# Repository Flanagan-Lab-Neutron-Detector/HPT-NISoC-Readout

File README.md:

# HPT-NISoC-Readout
PCB files for HighPoint Design's NISoC readout board (P/N 31813).

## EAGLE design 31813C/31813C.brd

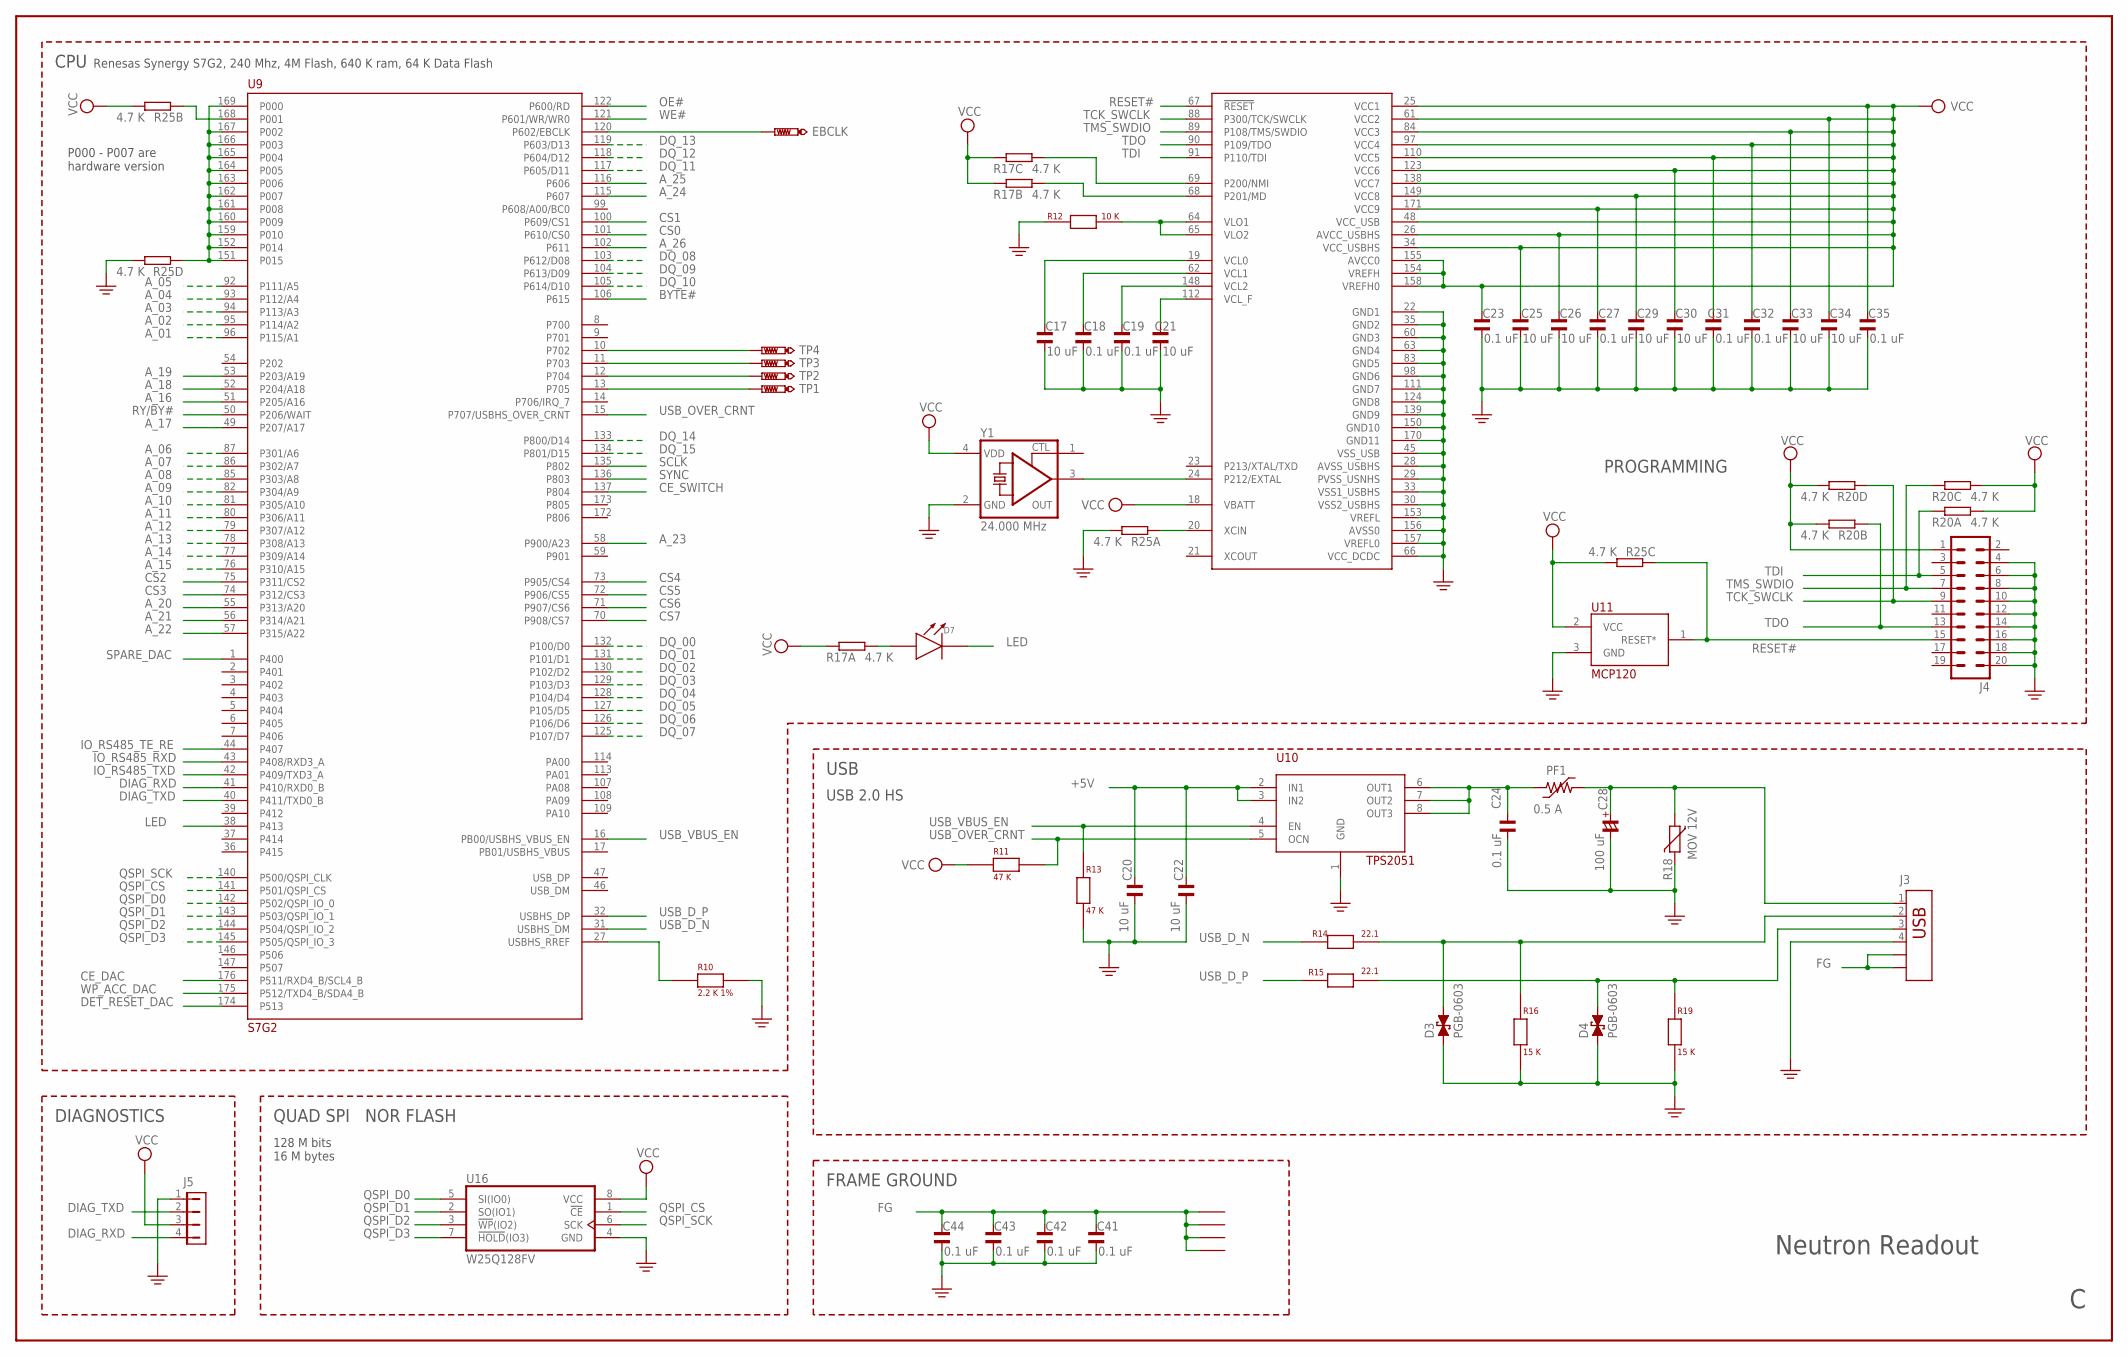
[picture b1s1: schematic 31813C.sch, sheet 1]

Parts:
C17, C20, C21, C22, C25, C26, C29, C30, C33, C34: 10 uF; 0603
C18, C19, C23, C24, C27, C31, C32, C35, C41, C42, C43, C44: 0.1 uF; 0603
C28: 100 uF; CSV-E/F
D3, D4: PGB-0603
D7: LED0805; D0805
EBCLK: TP; TP8040
J3: CON-USB-292303-1; USB
J4: ML20
J5: MTA04; MTA04-100
M1, M2, M3, M4: MNT-125
PF1: 0.5 A; F1206
R10: 2.2 K 1%; 0603
R11, R13: 47 K; 0603
R12: 10 K; 0603
R14, R15: 22.1; 0603
R16, R19: 15 K; 0603
R17, R20, R25: 4.7 K; RNET-4R-38V
R18: MOV 12V; R0603
TP1, TP2, TP3, TP4: TP; TP8040
U9: S7G2; LQFP176
U10: TPS2051; SOIC-8-SPECIAL
U11: MCP120; SOT23
U16: W25Q128FV; SO08-JB
Y1: 24.000 MHz; ASFL1

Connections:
+5V: C20.2, C22.2, U10.2 (IN1), U10.3 (IN2); also elsewhere on the board
A_01: U9.96 (P115/A1); also elsewhere on the board
A_02: U9.95 (P114/A2); also elsewhere on the board
A_03: U9.94 (P113/A3); also elsewhere on the board
A_04: U9.93 (P112/A4); also elsewhere on the board
A_05: U9.92 (P111/A5); also elsewhere on the board
A_06: U9.87 (P301/A6); also elsewhere on the board
A_07: U9.86 (P302/A7); also elsewhere on the board
A_08: U9.85 (P303/A8); also elsewhere on the board
A_09: U9.82 (P304/A9); also elsewhere on the board
A_10: U9.81 (P305/A10); also elsewhere on the board
A_11: U9.80 (P306/A11); also elsewhere on the board
A_12: U9.79 (P307/A12); also elsewhere on the board
A_13: U9.78 (P308/A13); also elsewhere on the board
A_14: U9.77 (P309/A14); also elsewhere on the board
A_15: U9.76 (P310/A15); also elsewhere on the board
A_16: U9.51 (P205/A16); also elsewhere on the board
A_17: U9.49 (P207/A17); also elsewhere on the board
A_18: U9.52 (P204/A18); also elsewhere on the board
A_19: U9.53 (P203/A19); also elsewhere on the board
A_20: U9.55 (P313/A20); also elsewhere on the board
A_21: U9.56 (P314/A21); also elsewhere on the board
A_22: U9.57 (P315/A22); also elsewhere on the board
A_23: U9.58 (P900/A23); also elsewhere on the board
A_24: U9.115 (P607); also elsewhere on the board
A_25: U9.116 (P606); also elsewhere on the board
A_26: U9.102 (P611); also elsewhere on the board
BYTE#: U9.106 (P615); also elsewhere on the board
CE_DAC: U9.176 (P511/RXD4_B/SCL4_B); also elsewhere on the board
CE_SWITCH: U9.137 (P804); also elsewhere on the board
CS0: U9.101 (P610/CS0); also elsewhere on the board
CS1: U9.100 (P609/CS1); also elsewhere on the board
CS2: U9.75 (P311/CS2); also elsewhere on the board
CS3: U9.74 (P312/CS3); also elsewhere on the board
CS4: U9.73 (P905/CS4); also elsewhere on the board
CS5: U9.72 (P906/CS5); also elsewhere on the board
CS6: U9.71 (P907/CS6); also elsewhere on the board
CS7: U9.70 (P908/CS7); also elsewhere on the board
DET_RESET_DAC: U9.174 (P513); also elsewhere on the board
DIAG_RXD: J5.4, U9.41 (P410/RXD0_B)
DIAG_TXD: J5.2, U9.40 (P411/TXD0_B)
DQ_00: U9.132 (P100/D0); also elsewhere on the board
DQ_01: U9.131 (P101/D1); also elsewhere on the board
DQ_02: U9.130 (P102/D2); also elsewhere on the board
DQ_03: U9.129 (P103/D3); also elsewhere on the board
DQ_04: U9.128 (P104/D4); also elsewhere on the board
DQ_05: U9.127 (P105/D5); also elsewhere on the board
DQ_06: U9.126 (P106/D6); also elsewhere on the board
DQ_07: U9.125 (P107/D7); also elsewhere on the board
DQ_08: U9.103 (P612/D08); also elsewhere on the board
DQ_09: U9.104 (P613/D09); also elsewhere on the board
DQ_10: U9.105 (P614/D10); also elsewhere on the board
DQ_11: U9.117 (P605/D11); also elsewhere on the board
DQ_12: U9.118 (P604/D12); also elsewhere on the board
DQ_13: U9.119 (P603/D13); also elsewhere on the board
DQ_14: U9.133 (P800/D14); also elsewhere on the board
DQ_15: U9.134 (P801/D15); also elsewhere on the board
FG: C41.2, C42.2, C43.2, C44.2, J3.S1, J3.S2, M1.1, M2.1, M3.1, M4.1
GND: C17.1, C18.1, C19.1, C20.1, C21.1, C22.1, C23.1, C24.1, C25.1, C26.1, C27.1, C28.-, C29.1, C30.1, C31.1, C32.1, C33.1, C34.1, C35.1, C41.1, C42.1, C43.1, C44.1, D3.1, D4.1, J3.4, J4.4, J4.6, J4.8, J4.10, J4.12, J4.14, J4.16, J4.18, J4.20, J5.1, R10.2, R12.1, R13.1, R16.1, R18.2, R19.1, R25.5 (2), R25.8 (2), U9.22 (GND1), U9.28 (AVSS_USBHS), U9.29 (PVSS_USNHS), U9.30 (VSS2_USBHS), U9.33 (VSS1_USBHS), U9.35 (GND2), U9.45 (VSS_USB), U9.60 (GND3), U9.63 (GND4), U9.66 (VCC_DCDC), U9.83 (GND5), U9.98 (GND6), U9.111 (GND7), U9.124 (GND8), U9.139 (GND9), U9.150 (GND10), U9.153 (VREFL), U9.156 (AVSS0), U9.157 (VREFL0), U9.170 (GND11), U10.1 (GND), U11.3 (GND), U16.4 (GND), Y1.2 (GND); also elsewhere on the board
IO_RS485_RXD: U9.43 (P408/RXD3_A); also elsewhere on the board
IO_RS485_TE_RE: U9.44 (P407); also elsewhere on the board
IO_RS485_TXD: U9.42 (P409/TXD3_A); also elsewhere on the board
LED: D7.C (1), U9.38 (P413)
unnamed: R12.2, U9.64 (VLO1), U9.65 (VLO2)
unnamed: R17.7 (2), U9.68 (P201/MD)
unnamed: R17.6 (2), U9.69 (P200/NMI)
unnamed: C17.2, U9.19 (VCL0)
unnamed: C18.2, U9.62 (VCL1)
unnamed: C19.2, U9.148 (VCL2)
unnamed: C21.2, U9.112 (VCL_F)
unnamed: U9.24 (P212/EXTAL), Y1.3 (OUT)
unnamed: C24.2, PF1.1, U10.6 (OUT1), U10.7 (OUT2), U10.8 (OUT3)
unnamed: C28.+, J3.1, PF1.2, R18.1
unnamed: D3.2, J3.2, R14.2, R16.2
unnamed: R10.1, U9.27 (USBHS_RREF)
unnamed: D4.2, J3.3, R15.2, R19.2
unnamed: TP3.1, U9.11 (P703)
unnamed: TP4.1, U9.10 (P702)
unnamed: TP1.1, U9.13 (P705)
unnamed: TP2.1, U9.12 (P704)
unnamed: R25.1, U9.20 (XCIN)
unnamed: D7.A (2), R17.8 (2)
unnamed: R25.2 (1), U9.168 (P001)
unnamed: R25.4 (1), U9.151 (P015), U9.152 (P014), U9.159 (P010), U9.160 (P009), U9.161 (P008), U9.162 (P007), U9.163 (P006), U9.164 (P005), U9.165 (P004), U9.166 (P003), U9.167 (P002), U9.169 (P000)
unnamed: EBCLK.1, U9.120 (P602/EBCLK)
OE#: U9.122 (P600/RD); also elsewhere on the board
QSPI_CS: U9.141 (P501/QSPI_CS), U16.1 (!CE!)
QSPI_D0: U9.142 (P502/QSPI_IO_0), U16.5 (SI(IO0))
QSPI_D1: U9.143 (P503/QSPI_IO_1), U16.2 (SO(IO1))
QSPI_D2: U9.144 (P504/QSPI_IO_2), U16.3 (!WP!(IO2))
QSPI_D3: U9.145 (P505/QSPI_IO_3), U16.7 (!HOLD!(IO3))
QSPI_SCK: U9.140 (P500/QSPI_CLK), U16.6 (SCK)
RESET#: J4.15, R25.3 (1), U9.67 (!RESET), U11.1 (RESET*)
RY/BY#: U9.50 (P206/WAIT); also elsewhere on the board
SCLK: U9.135 (P802); also elsewhere on the board
SPARE_DAC: U9.1 (P400); also elsewhere on the board
SYNC: U9.136 (P803); also elsewhere on the board
TCK_SWCLK: J4.9, R20.4 (1), U9.88 (P300/TCK/SWCLK)
TDI: J4.5, R20.1, U9.91 (P110/TDI)
TDO: J4.13, R20.2 (1), U9.90 (P109/TDO)
TMS_SWDIO: J4.7, R20.3 (1), U9.89 (P108/TMS/SWDIO)
USB_D_N: R14.1, U9.31 (USBHS_DM)
USB_D_P: R15.1, U9.32 (USBHS_DP)
USB_OVER_CRNT: R11.2, U9.15 (P707/USBHS_OVER_CRNT), U10.5 (OCN)
USB_VBUS_EN: R13.2, U9.16 (PB00/USBHS_VBUS_EN), U10.4 (EN)
VCC: C23.2, C25.2, C26.2, C27.2, C29.2, C30.2, C31.2, C32.2, C33.2, C34.2, C35.2, J4.1, J5.3, R11.1, R17.1, R17.2 (1), R17.3 (1), R20.5 (2), R20.6 (2), R20.7 (2), R20.8 (2), R25.6 (2), R25.7 (2), U9.18 (VBATT), U9.25 (VCC1), U9.26 (AVCC_USBHS), U9.34 (VCC_USBHS), U9.48 (VCC_USB), U9.61 (VCC2), U9.84 (VCC3), U9.97 (VCC4), U9.110 (VCC5), U9.123 (VCC6), U9.138 (VCC7), U9.149 (VCC8), U9.154 (VREFH), U9.155 (AVCC0), U9.158 (VREFH0), U9.171 (VCC9), U11.2 (VCC), U16.8 (VCC), Y1.4 (VDD); also elsewhere on the board
WE#: U9.121 (P601/WR/WR0); also elsewhere on the board
WP_ACC_DAC: U9.175 (P512/TXD4_B/SDA4_B); also elsewhere on the board

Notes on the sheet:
PROGRAMMING
CPU
Renesas Synergy S7G2, 240 Mhz, 4M Flash, 640 K ram, 64 K Data Flash
Neutron Readout
USB
QUAD SPI NOR FLASH
128 M bits 16 M bytes
DIAGNOSTICS
FRAME GROUND
USB 2.0 HS
P000 - P007 are hardware version

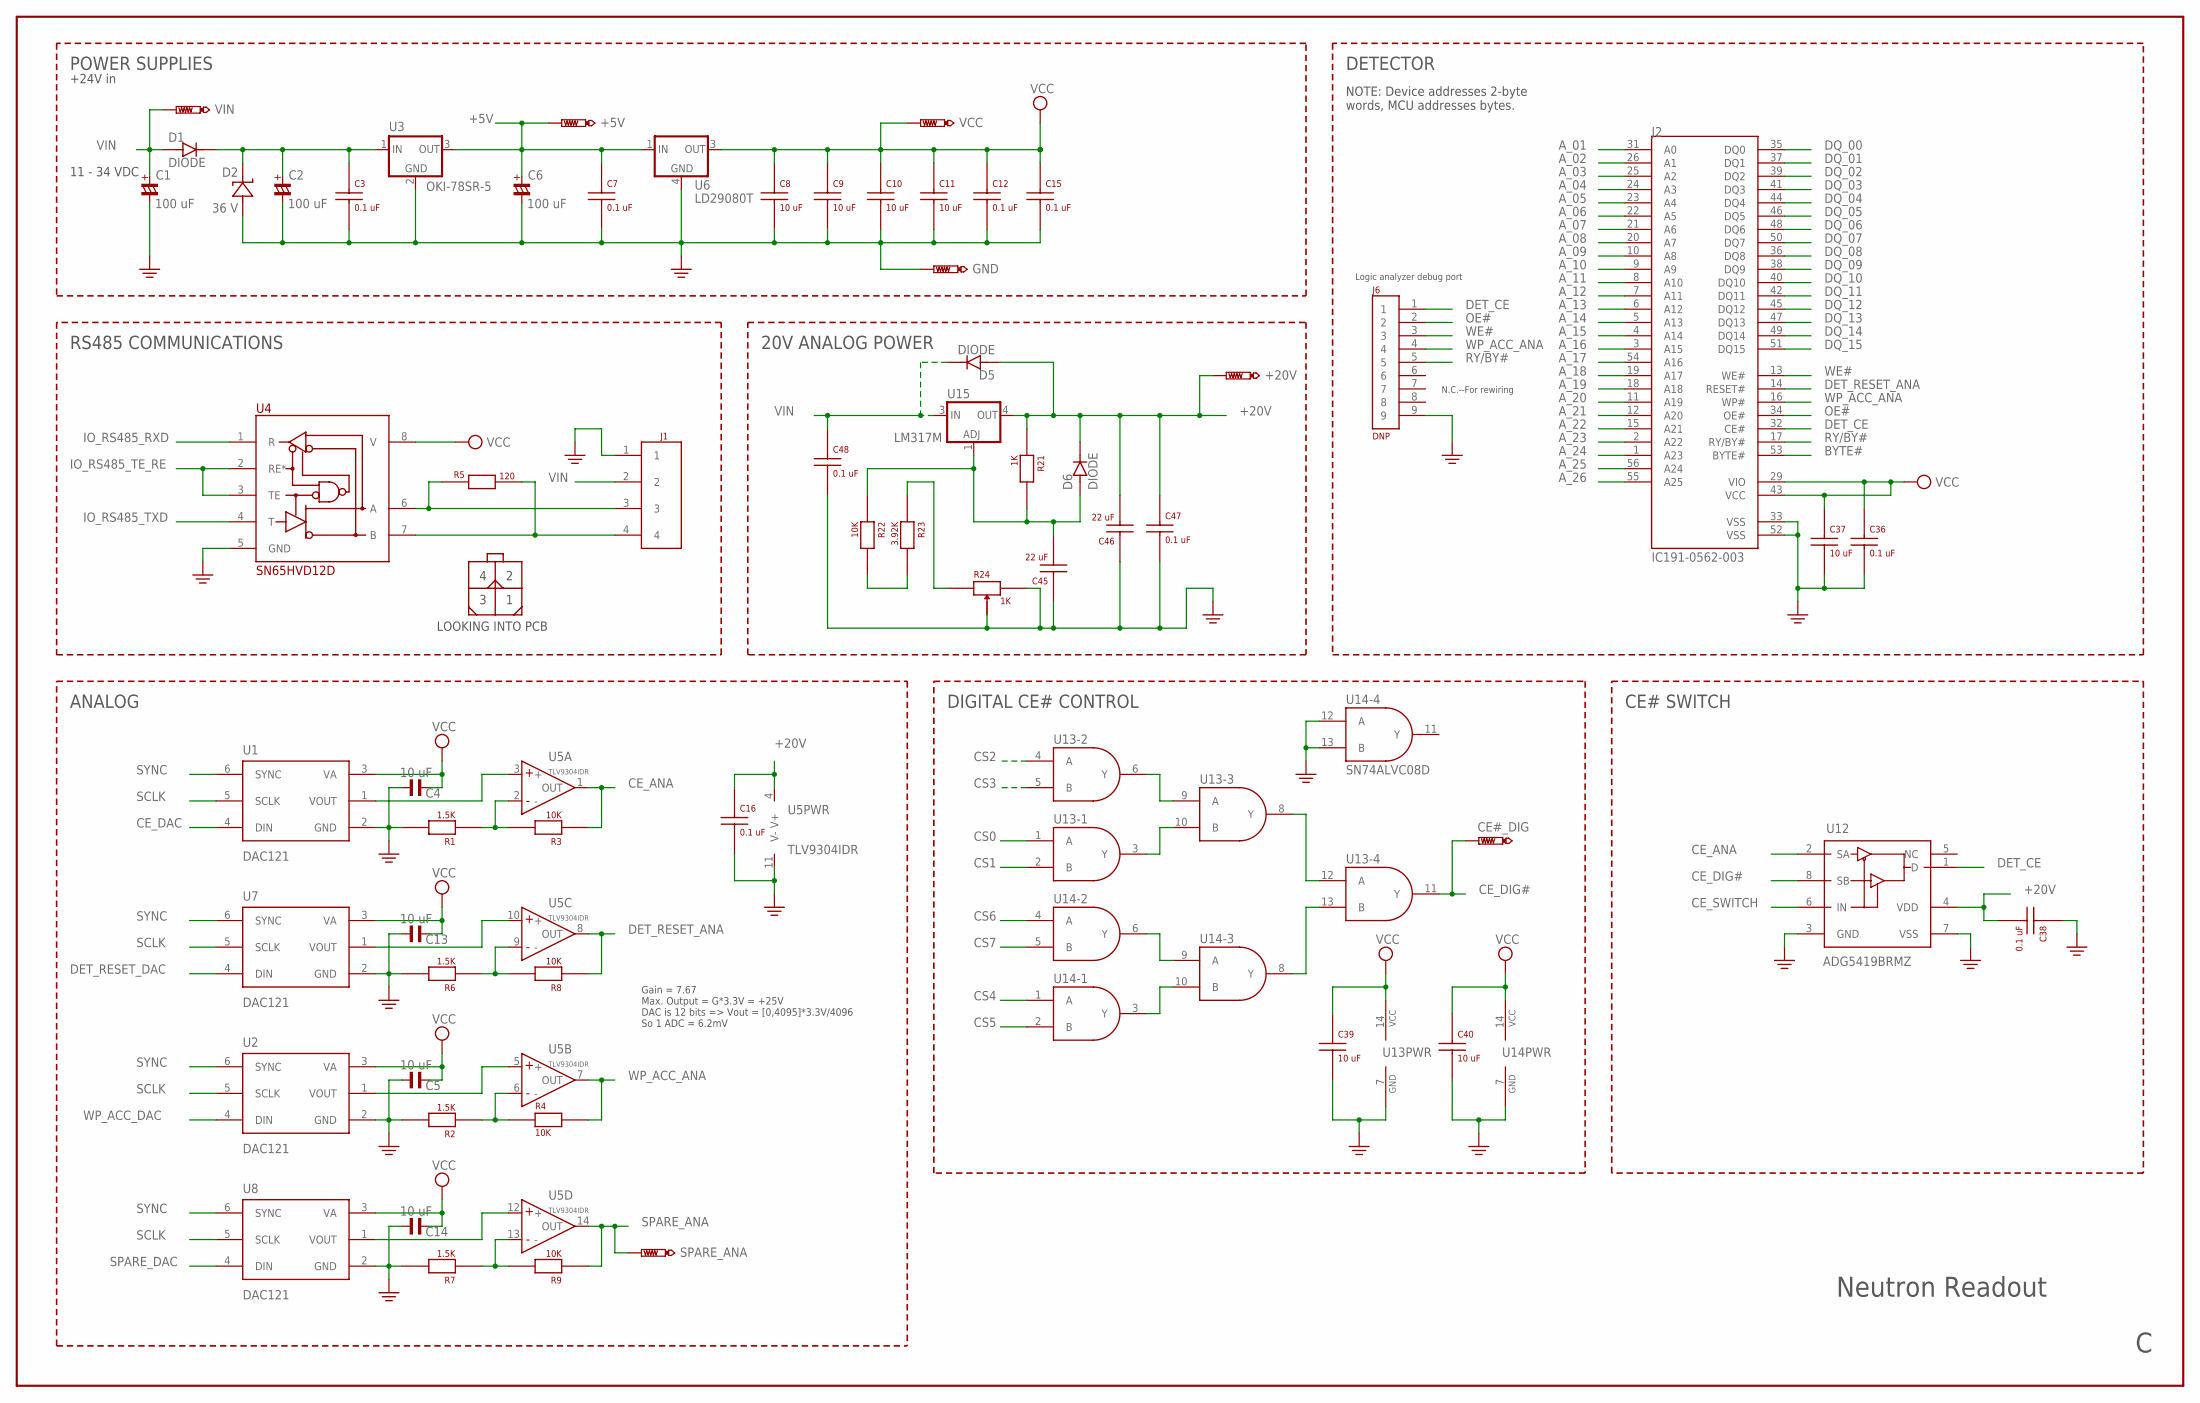
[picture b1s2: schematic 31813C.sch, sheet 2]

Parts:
+5V, +20V: TP; TP8040
C1, C2, C6: 100 uF; CSV-E/F
C3, C7, C12, C15, C16, C36, C38, C47, C48: 0.1 uF; 0603
C4, C5, C8, C9, C10, C11, C13, C14, C37, C39, C40: 10 uF; 0603
C45, C46: 22 uF; C1206
CE#_DIG: TP; TP8040
D1, D5, D6: DIODE; SOD-123_MINI-SMA
D2: 36 V; SMB
GND: TP; TP8040
J1: MICRO-FIT-4POS; 43045-0412
J2: IC191-0562-003; IC1910562003
J6: DNP; 9P-100
R1, R2, R6, R7: 1.5K; 0603
R3, R4, R8, R9, R22: 10K; 0603
R5: 120; 0603
R21: 1K; 0603
R23: 3.92K; 0603
R24: 1K; POT-V10
SPARE_ANA: TP; TP8040
U1, U2, U7, U8: DAC121; SOT23-6
U3: OKI-78SR-5; PS-OKI-78SR
U4: SN65HVD12D; SOIC-08-150
U5: TLV9304IDR; SO14
U6: LD29080T; DPAK
U12: ADG5419BRMZ; RM_8_ADI
U13, U14: SN74ALVC08D; D14
U15: LM317M; DPAK
VCC: TP; TP8040
VIN: TP; TP8040

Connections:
+5V: +5V.1, C6.+, C7.1, U3.3 (OUT), U6.1 (IN); also elsewhere on the board
+20V: +20V.1, C16.1, C38.2, C46.2, C47.1, D5.A, D6.C, R21.1, U5.4 (V+), U12.4 (VDD), U15.4 (OUT)
A_01: J2.31 (A0); also elsewhere on the board
A_02: J2.26 (A1); also elsewhere on the board
A_03: J2.25 (A2); also elsewhere on the board
A_04: J2.24 (A3); also elsewhere on the board
A_05: J2.23 (A4); also elsewhere on the board
A_06: J2.22 (A5); also elsewhere on the board
A_07: J2.21 (A6); also elsewhere on the board
A_08: J2.20 (A7); also elsewhere on the board
A_09: J2.10 (A8); also elsewhere on the board
A_10: J2.9 (A9); also elsewhere on the board
A_11: J2.8 (A10); also elsewhere on the board
A_12: J2.7 (A11); also elsewhere on the board
A_13: J2.6 (A12); also elsewhere on the board
A_14: J2.5 (A13); also elsewhere on the board
A_15: J2.4 (A14); also elsewhere on the board
A_16: J2.3 (A15); also elsewhere on the board
A_17: J2.54 (A16); also elsewhere on the board
A_18: J2.19 (A17); also elsewhere on the board
A_19: J2.18 (A18); also elsewhere on the board
A_20: J2.11 (A19); also elsewhere on the board
A_21: J2.12 (A20); also elsewhere on the board
A_22: J2.15 (A21); also elsewhere on the board
A_23: J2.2 (A22); also elsewhere on the board
A_24: J2.1 (A23); also elsewhere on the board
A_25: J2.56 (A24); also elsewhere on the board
A_26: J2.55 (A25); also elsewhere on the board
BYTE#: J2.53 (BYTE#); also elsewhere on the board
CE_ANA: R3.1, U5.1 (OUT), U12.2 (SA)
CE_DAC: U1.4 (DIN); also elsewhere on the board
CE_DIG#: CE#_DIG.1, U12.8 (SB), U13.11 (Y)
CE_SWITCH: U12.6 (IN); also elsewhere on the board
CS0: U13.1 (A); also elsewhere on the board
CS1: U13.2 (B); also elsewhere on the board
CS2: U13.4 (A); also elsewhere on the board
CS3: U13.5 (B); also elsewhere on the board
CS4: U14.1 (A); also elsewhere on the board
CS5: U14.2 (B); also elsewhere on the board
CS6: U14.4 (A); also elsewhere on the board
CS7: U14.5 (B); also elsewhere on the board
DATA_N: J1.4, R5.2, U4.7 (B)
DATA_P: J1.3, R5.1, U4.6 (A)
DET_CE: J2.32 (CE#), J6.1, U12.1 (D)
DET_RESET_ANA: J2.14 (RESET#), R8.1, U5.8 (OUT)
DET_RESET_DAC: U7.4 (DIN); also elsewhere on the board
DQ_00: J2.35 (DQ0); also elsewhere on the board
DQ_01: J2.37 (DQ1); also elsewhere on the board
DQ_02: J2.39 (DQ2); also elsewhere on the board
DQ_03: J2.41 (DQ3); also elsewhere on the board
DQ_04: J2.44 (DQ4); also elsewhere on the board
DQ_05: J2.46 (DQ5); also elsewhere on the board
DQ_06: J2.48 (DQ6); also elsewhere on the board
DQ_07: J2.50 (DQ7); also elsewhere on the board
DQ_08: J2.36 (DQ8); also elsewhere on the board
DQ_09: J2.38 (DQ9); also elsewhere on the board
DQ_10: J2.40 (DQ10); also elsewhere on the board
DQ_11: J2.42 (DQ11); also elsewhere on the board
DQ_12: J2.45 (DQ12); also elsewhere on the board
DQ_13: J2.47 (DQ13); also elsewhere on the board
DQ_14: J2.49 (DQ14); also elsewhere on the board
DQ_15: J2.51 (DQ15); also elsewhere on the board
GND: C1.-, C2.-, C3.2, C4.1, C5.1, C6.-, C7.2, C8.2, C9.2, C10.2, C11.2, C12.2, C13.1, C14.1, C15.2, C16.2, C36.2, C37.2, C38.1, C39.2, C40.2, C45.1, C46.1, C47.2, C48.2, D2.A, GND.1, J1.1, J2.33 (VSS), J2.52 (VSS), J6.9, R1.2, R2.2, R6.2, R7.2, R24.2, R24.3, U1.2 (GND), U2.2 (GND), U3.2 (GND), U4.5 (GND), U5.11 (V-), U6.4 (GND), U7.2 (GND), U8.2 (GND), U12.3 (GND), U12.7 (VSS), U13.7 (GND), U14.7 (GND), U14.12 (A), U14.13 (B); also elsewhere on the board
IO_RS485_RXD: U4.1 (R); also elsewhere on the board
IO_RS485_TE_RE: U4.2 (RE*), U4.3 (TE); also elsewhere on the board
IO_RS485_TXD: U4.4 (T); also elsewhere on the board
unnamed: U1.1 (VOUT), U5.3 (+)
unnamed: U5.10 (+), U7.1 (VOUT)
unnamed: R1.1, R3.2, U5.2 (-)
unnamed: U2.1 (VOUT), U5.5 (+)
unnamed: R6.1, R8.2, U5.9 (-)
unnamed: R2.1, R4.1, U5.6 (-)
unnamed: U5.12 (+), U8.1 (VOUT)
unnamed: R7.1, R9.2, U5.13 (-)
unnamed: C2.+, C3.1, D1.C, D2.C, U3.1 (IN)
unnamed: U13.6 (Y), U13.9 (A)
unnamed: U13.3 (Y), U13.10 (B)
unnamed: U14.6 (Y), U14.9 (A)
unnamed: U14.3 (Y), U14.10 (B)
unnamed: U13.8 (Y), U13.12 (A)
unnamed: U13.13 (B), U14.8 (Y)
unnamed: C45.2, D6.A, R21.2, R22.1, U15.1 (ADJ)
unnamed: R22.2, R23.2
unnamed: R23.1, R24.1
OE#: J2.34 (OE#), J6.2; also elsewhere on the board
RY/BY#: J2.17 (RY/BY#), J6.5; also elsewhere on the board
SCLK: U1.5 (SCLK), U2.5 (SCLK), U7.5 (SCLK), U8.5 (SCLK); also elsewhere on the board
SPARE_ANA: R9.1, SPARE_ANA.1, U5.14 (OUT)
SPARE_DAC: U8.4 (DIN); also elsewhere on the board
SYNC: U1.6 (SYNC), U2.6 (SYNC), U7.6 (SYNC), U8.6 (SYNC); also elsewhere on the board
VCC: C4.2, C5.2, C8.1, C9.1, C10.1, C11.1, C12.1, C13.2, C14.2, C15.1, C36.1, C37.1, C39.1, C40.1, J2.29 (VIO), J2.43 (VCC), U1.3 (VA), U2.3 (VA), U4.8 (V), U6.3 (OUT), U7.3 (VA), U8.3 (VA), U13.14 (VCC), U14.14 (VCC), VCC.1; also elsewhere on the board
VIN: C1.+, C48.1, D1.A, D5.C, J1.2, U15.3 (IN), VIN.1
WE#: J2.13 (WE#), J6.3; also elsewhere on the board
WP_ACC_ANA: J2.16 (WP#), J6.4, R4.2, U5.7 (OUT)
WP_ACC_DAC: U2.4 (DIN); also elsewhere on the board

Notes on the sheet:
11 - 34 VDC
Neutron Readout
POWER SUPPLIES
RS485 COMMUNICATIONS
DETECTOR
ANALOG
+24V in
DIGITAL CE# CONTROL
CE# SWITCH
20V ANALOG POWER
NOTE: Device addresses 2-byte words, MCU addresses bytes.
N.C.--For rewiring
Logic analyzer debug port
Gain = 7.67 Max. Output = G*3.3V = +25V DAC is 12 bits => Vout = [0,4095]*3.3V/4096 So 1 ADC = 6.2mV

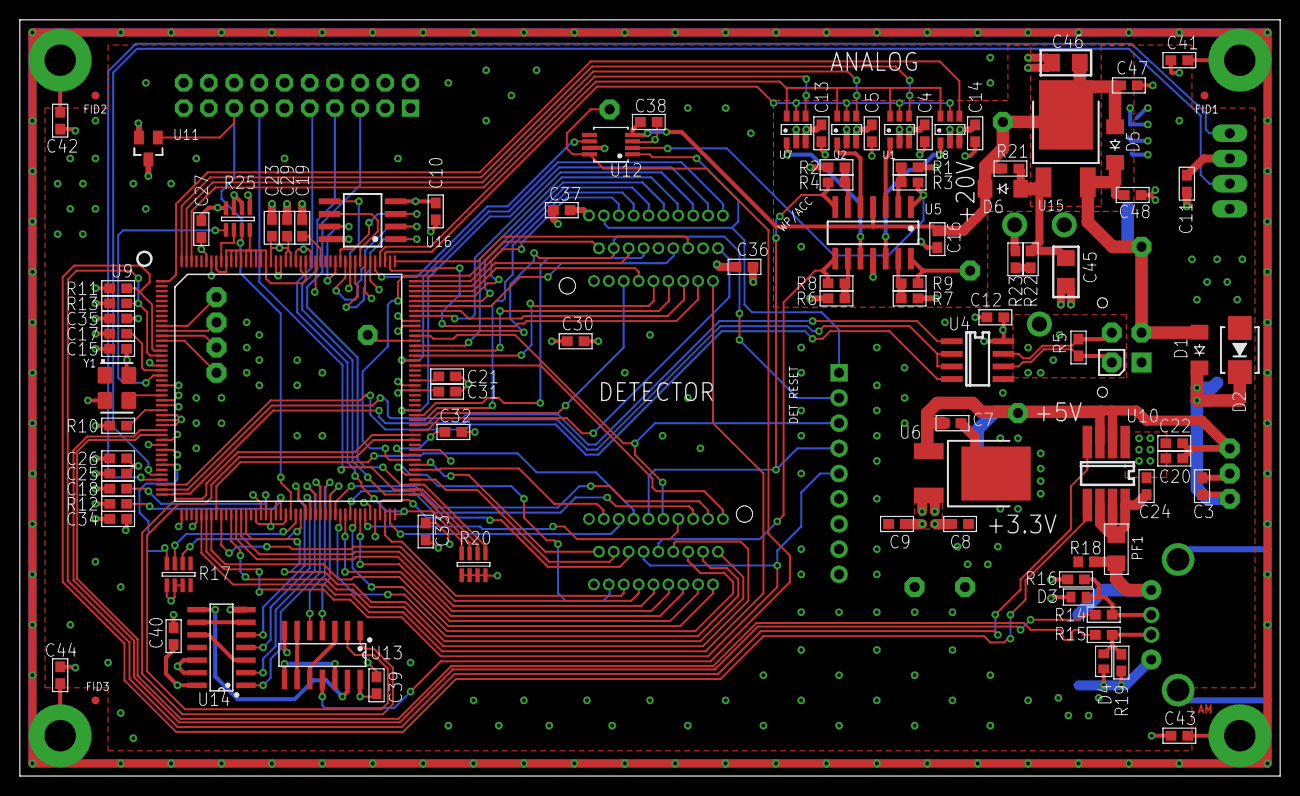
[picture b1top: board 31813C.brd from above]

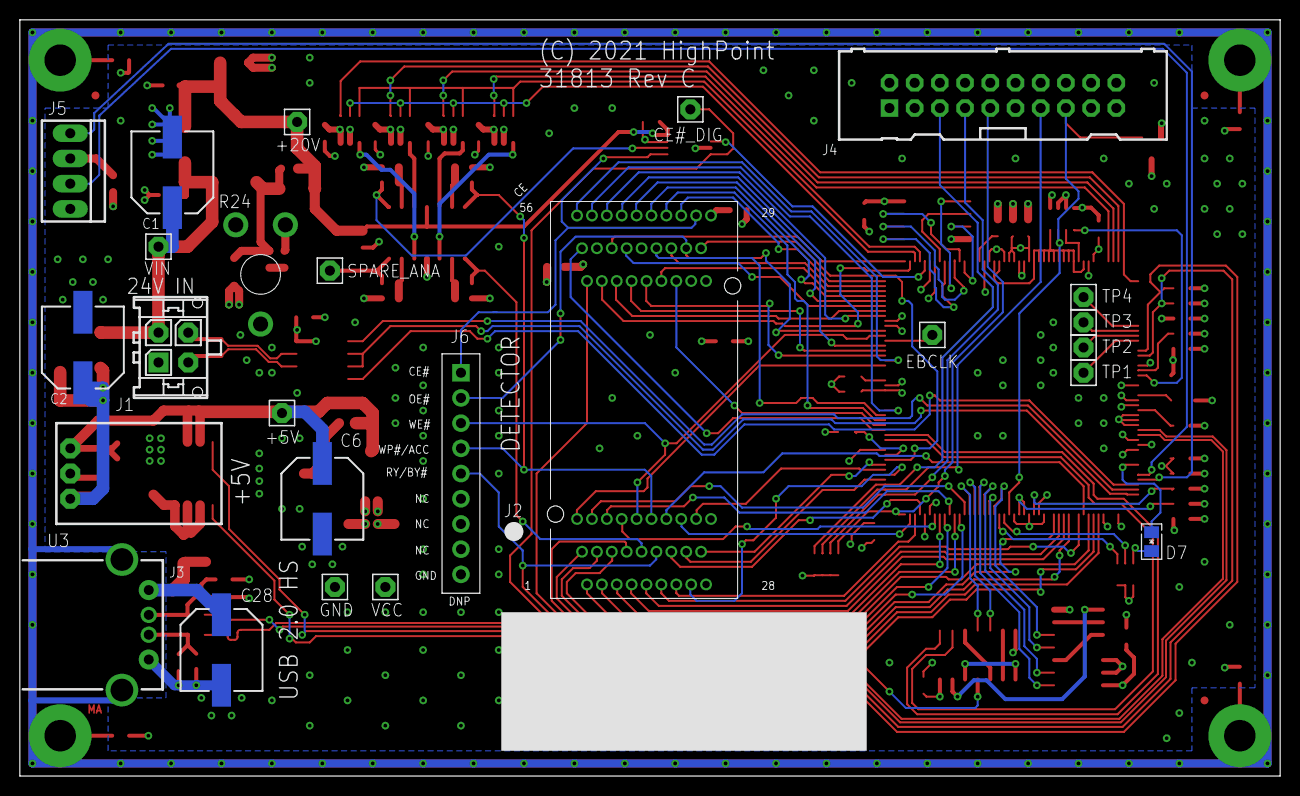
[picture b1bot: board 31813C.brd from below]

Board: 4 copper layers, 127.0 x 76.2 mm, 123 parts (25 on the bottom side), 136 nets.

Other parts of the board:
FID1, FID2, FID3: G8

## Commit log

2022-06-02 Initiam commit
2022-06-02 Added 31813B schematic PDF

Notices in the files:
31813C/31813C.brd:
(C) 2021 HighPoint
parts and their libraries:
HighPoint_Frames: (c) 2021
